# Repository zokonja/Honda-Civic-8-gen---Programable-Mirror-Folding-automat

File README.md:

Custom designed automat for Honda Civic 8gen for automatic mirrors fold/unfold.
Automat is programable and can be set to 5 different programs (behaviour actions).
Inside is complete device schematic (based on Microchip PIC 12F1501 micro) and firmware written in assembler and compiled HEX file for 12F1501.
Installation and demonstration video: https://youtu.be/eVyPs17ZJMc

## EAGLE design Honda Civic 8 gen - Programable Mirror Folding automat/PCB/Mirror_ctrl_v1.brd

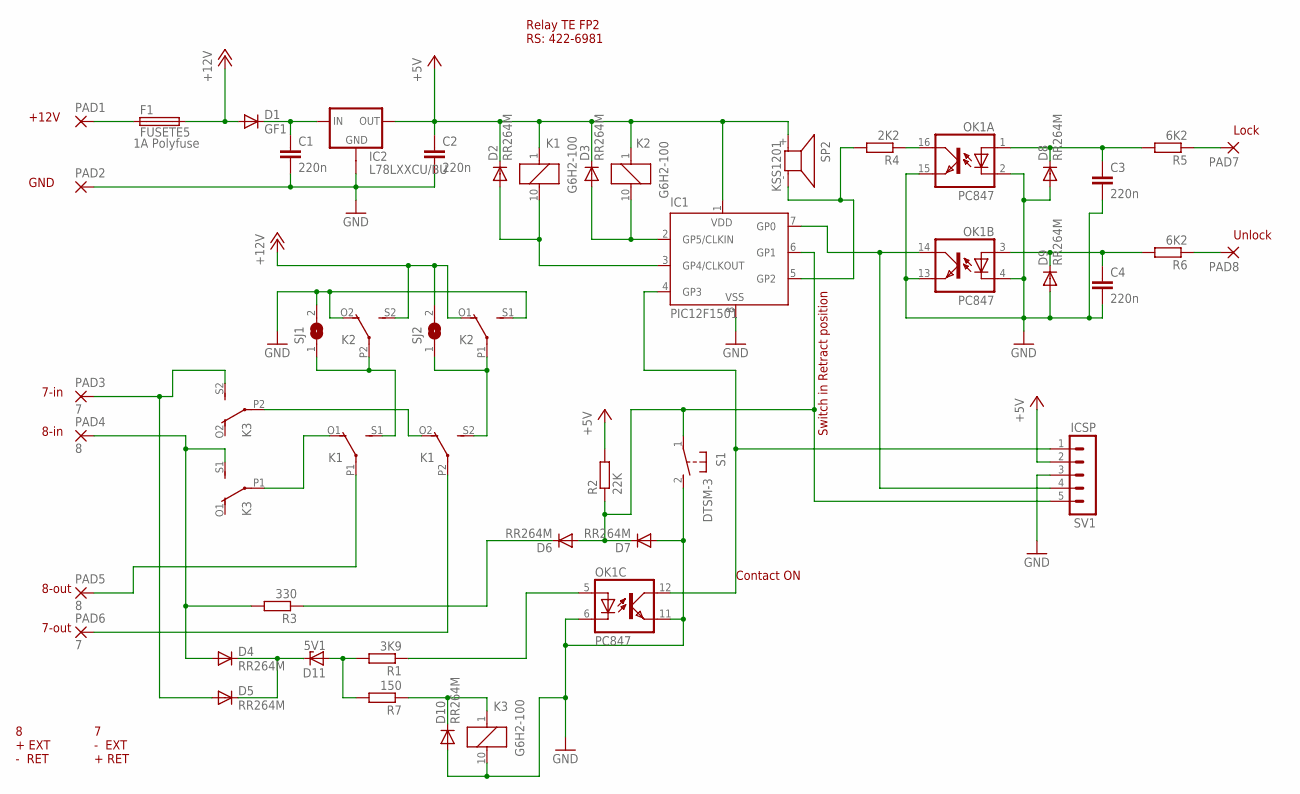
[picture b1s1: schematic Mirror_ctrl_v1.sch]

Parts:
C1, C2, C3, C4: 220n; C1206
D1: GF1; DO214BA
D2, D3, D4, D5, D6, D7, D8, D9, D10: RR264M; SOD-123_MINI-SMA
D11: 5V1; SOD80C
F1: FUSETE5; TE5
IC1: PIC12F1501; DIL8
IC2: L78LXXCU/BU; SOT89
K1, K2, K3: G6H2-100
OK1: PC847; DIL16
PAD1, PAD2, PAD7, PAD8: 3,81/1,4
PAD3, PAD6: 7; 3,81/1,4
PAD4, PAD5: 8; 3,81/1,4
R1: 3K9; R1206
R2: 22K; R1206
R3: 330; R1206
R4: 2K2; R1206
R5, R6: 6K2; R1206
R7: 150; R1206
S1: DTSM-3
SJ1, SJ2: SJ
SP2: KSS1201
SV1: ICSP; MA05-1

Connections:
+5V: C2.1, D2.C, D3.C, IC1.1 (VDD), IC2.1 (OUT), K1.1, K2.1, R2.2, SP2.+ (1), SV1.2
+12V: D1.A, F1.2, K2.O1 (O), K2.S2 (S), SJ2.2
GND: C1.2, C2.2, C3.2, C4.2, D7.A, D8.A, D9.A, D10.A, IC1.8 (VSS), IC2.4 (GND1), K2.O2 (O), K2.S1 (S), K3.10 (2), OK1.2 (C), OK1.4 (C), OK1.6 (C), OK1.11 (EMIT), OK1.13 (EMIT), OK1.15 (EMIT), PAD2.1, S1.2, SJ1.2, SV1.3
unnamed: D3.A, IC1.2 (GP5/CLKIN), K2.10 (2)
unnamed: C1.1, D1.C, IC2.3 (IN)
unnamed: F1.1, PAD1.1
unnamed: C3.1, D8.C, OK1.1 (A), R5.2
unnamed: D4.A, K3.S1 (S), PAD4.1, R3.2
unnamed: D5.A, K3.S2 (S), PAD3.1
unnamed: K1.P1, PAD5.1
unnamed: K1.P2, PAD6.1
unnamed: PAD7.1, R5.1
unnamed: D2.A, IC1.3 (GP4/CLKOUT), K1.10 (2)
unnamed: OK1.5 (A), R1.1
unnamed: D11.A, R1.2, R7.2
unnamed: K1.S1 (S), K2.P2, SJ1.1
unnamed: PAD8.1, R6.1
unnamed: K1.S2 (S), K2.P1, SJ2.1
unnamed: C4.1, D9.C, OK1.3 (A), R6.2
unnamed: IC1.4 (GP3), OK1.12 (COL), SV1.1
unnamed: IC1.7 (GP0), OK1.14 (COL), SV1.4
unnamed: OK1.16 (COL), R4.1
unnamed: D6.C, R3.1
unnamed: IC1.5 (GP2), R4.2, SP2.- (2)
unnamed: D6.A, D7.C, IC1.6 (GP1), R2.1, S1.1, SV1.5
unnamed: K1.O2 (O), K3.P2
unnamed: D10.C, K3.1, R7.1
unnamed: K1.O1 (O), K3.P1
unnamed: D4.C, D5.C, D11.C

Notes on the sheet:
+12V
GND
7-in
8-in
8-out
7-out
Lock
Unlock
Contact ON
1A Polyfuse
Switch in Retract position
Relay TE FP2 RS: 422-6981
8 + EXT - RET
7 - EXT + RET

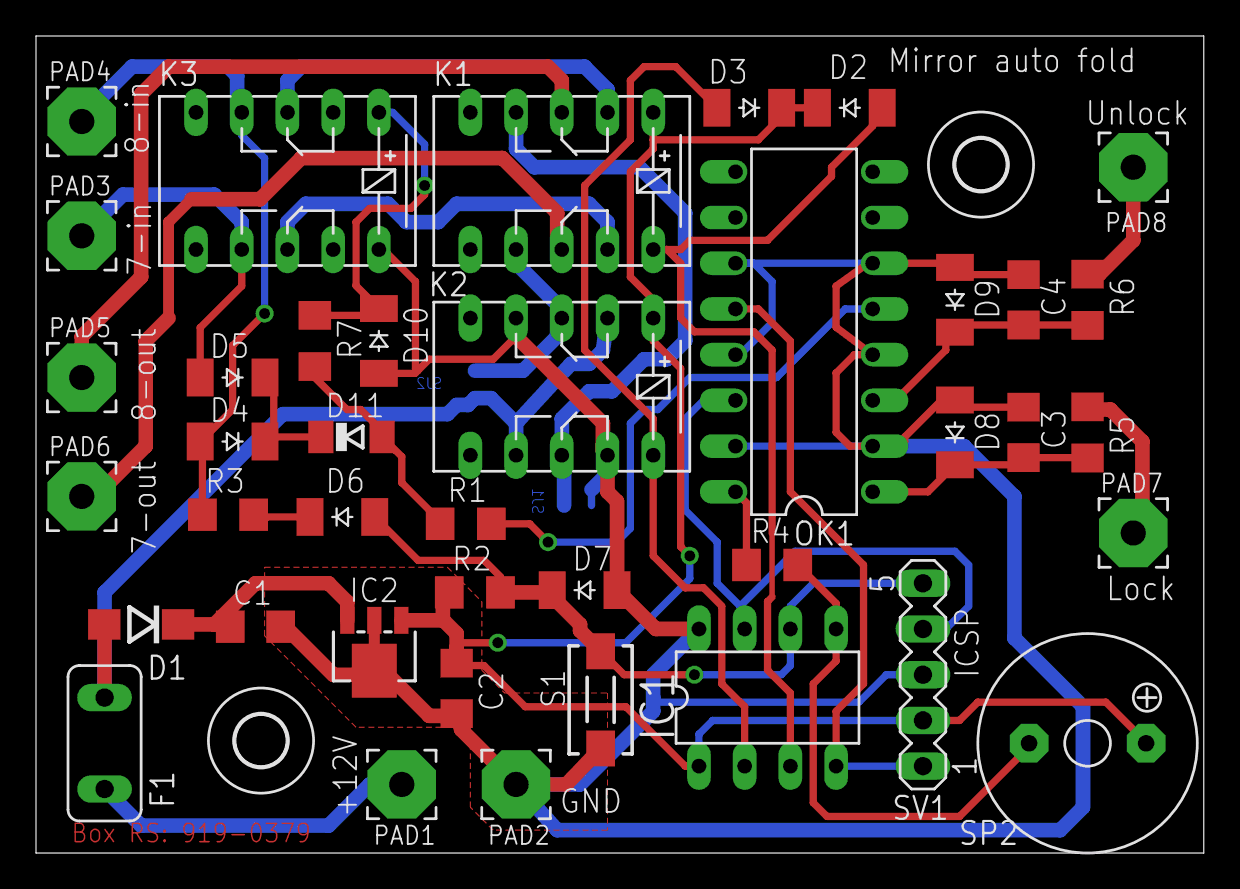
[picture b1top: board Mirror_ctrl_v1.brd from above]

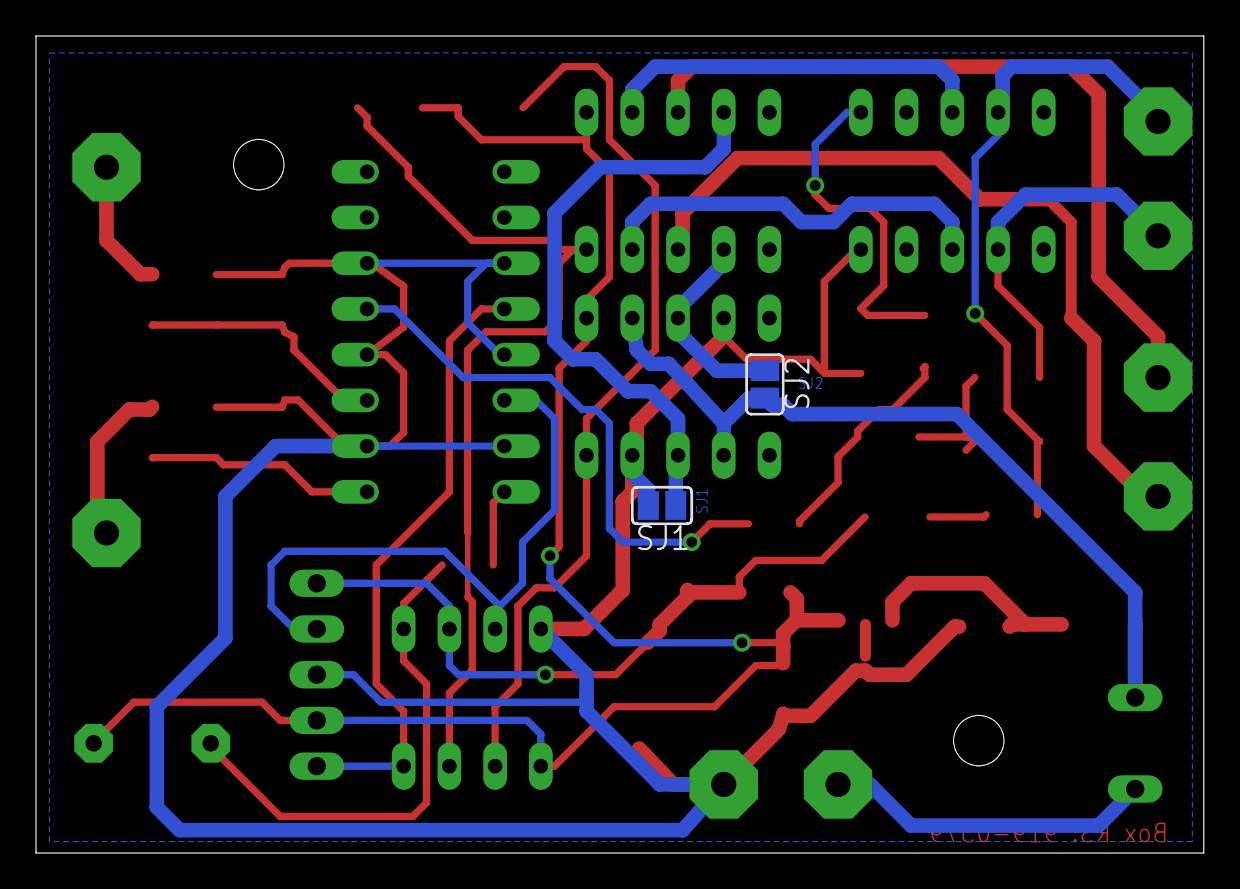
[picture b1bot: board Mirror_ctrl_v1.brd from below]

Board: 2 copper layers, 64.9 x 45.4 mm, 44 parts (2 on the bottom side), 29 nets.

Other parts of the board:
U$1, U$3: 2,8
